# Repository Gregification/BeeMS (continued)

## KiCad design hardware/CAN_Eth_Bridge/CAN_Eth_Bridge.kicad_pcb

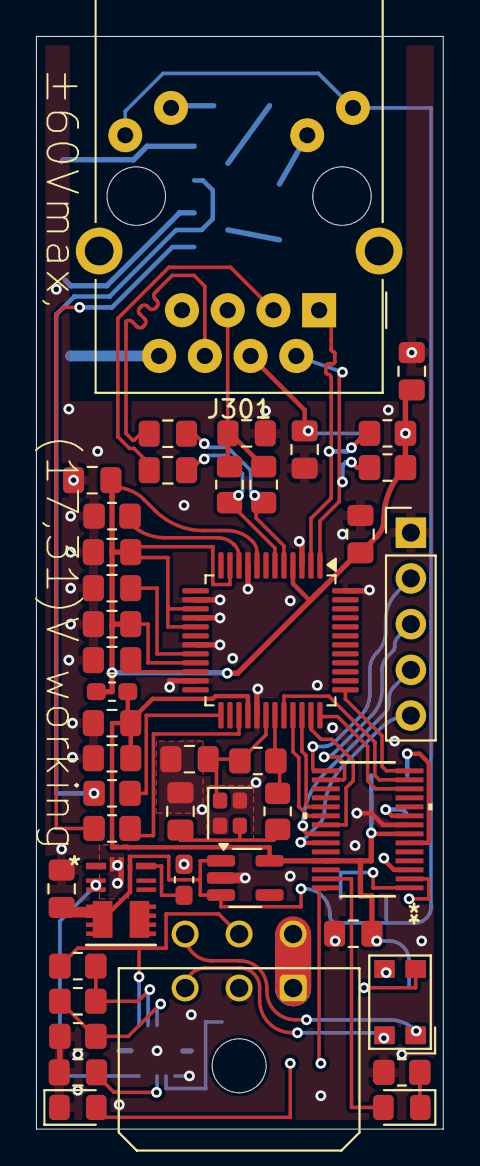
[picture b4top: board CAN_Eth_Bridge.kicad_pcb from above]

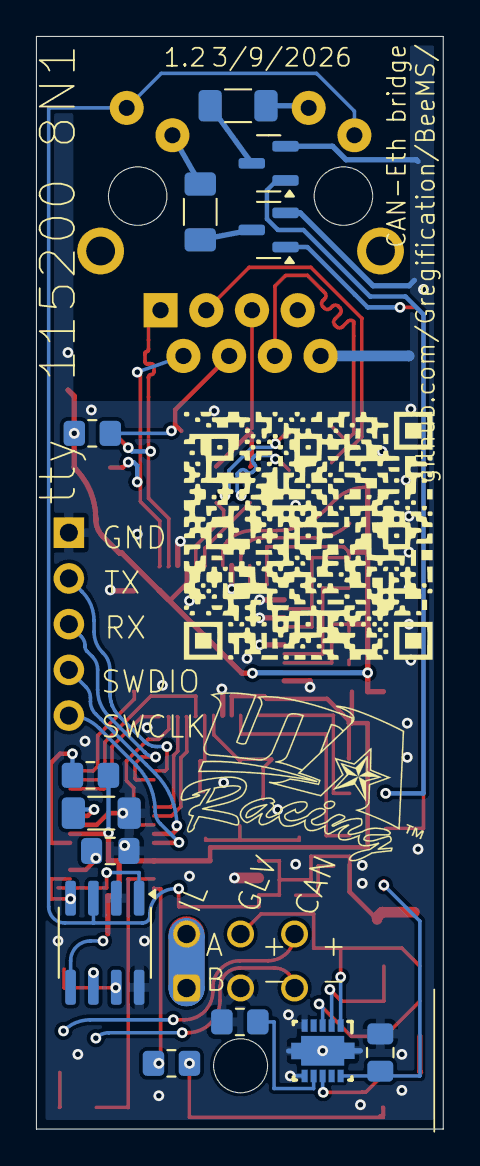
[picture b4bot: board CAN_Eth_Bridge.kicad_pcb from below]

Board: 2 copper layers, 22.6 x 60.7 mm, 57 parts (13 on the bottom side), 57 nets.

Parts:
C101: 1u; C_0603_1608Metric_Pad1.08x0.95mm_HandSolder
C102, C312, C319: 10n; C_0805_2012Metric_Pad1.18x1.45mm_HandSolder
C103, C105, C302, C309: 22u; C_0805_2012Metric_Pad1.18x1.45mm_HandSolder
C106, C110, C301, C304, C305, C311, C313: 220n; C_0805_2012Metric_Pad1.18x1.45mm_HandSolder
C303, C306: 18p; C_0805_2012Metric_Pad1.18x1.45mm_HandSolder
C314: 4.7u; C_0805_2012Metric_Pad1.18x1.45mm_HandSolder
C316, C317: 6.8n; C_0805_2012Metric_Pad1.18x1.45mm_HandSolder
C318: 22n; C_0805_2012Metric_Pad1.18x1.45mm_HandSolder
D102: green; LED_0805_2012Metric_Pad1.15x1.40mm_HandSolder
D105: blue; LED_0805_2012Metric_Pad1.15x1.40mm_HandSolder
FB301: MH1608-151Y; L_0603_1608Metric_Pad1.05x0.95mm_HandSolder
FL101: Choke_CommonMode_FerriteCore_1243; L_CommonModeChoke_Coilcraft_1812CAN
J101: Global LV and CAN; Molex_Micro-Fit_3.0_43045-0600_2x03_P3.00mm_Horizontal
J102: Conn_01x05_Pin; PinHeader_1x05_P2.54mm_Vertical
J301: RJ45_Amphenol_RJMG1BD3B8K1ANR
Q301, Q302: MMBT5550L; SOT-23
R101: 22.1k; R_0805_2012Metric_Pad1.20x1.40mm_HandSolder
R102, R103, R104, R311, R312: 2.4k; R_0805_2012Metric_Pad1.20x1.40mm_HandSolder
R105: 100k; R_1206_3216Metric_Pad1.30x1.75mm_HandSolder
R106: 40.2k; R_0805_2012Metric_Pad1.20x1.40mm_HandSolder
R107, R301: 1M; R_0805_2012Metric_Pad1.20x1.40mm_HandSolder
R108: 33.2k; R_0805_2012Metric_Pad1.20x1.40mm_HandSolder
R302, R315: 10; R_0805_2012Metric_Pad1.20x1.40mm_HandSolder
R303: 12.4k; R_0805_2012Metric_Pad1.20x1.40mm_HandSolder
R309, R310, R313, R314: 49.9; R_0805_2012Metric_Pad1.20x1.40mm_HandSolder
R316, R317: 750; R_1206_3216Metric_Pad1.30x1.75mm_HandSolder
U101: TPSM33606S5QRDNRQ1; RDN0011A_TEX
U102: TPS26625DRCR; DRC0010J_NV
U103: MCP2542FDxMF; SOIC-8_3.9x4.9mm_P1.27mm
U104: XMSM0G3507SDGS28R; VSSOP28_DGS_TEX-M
U106: NCP163ASN330T1G; SOT-23-5_HandSoldering
U301: W5500; LQFP-48_7x7mm_P0.5mm
Y301: Crystal_GND24; Crystal_SMD_2016-4Pin_2.0x1.6mm

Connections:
+3.3V: C105.1, C309.1, C313.1, FB301.1, R104.2, U103.5 (VIO), U104.7 (VDD), U104.25 (PA22/CLK_OUT/A0_7), U106.5 (VOUT), U301.28 (VDD)
+5V: C103.1, J301.L1, J301.L4, U101.4 (VOUT), U101.9 (FB), U103.3 (VDD), U106.1 (VIN), U106.3 (EN)
/Ethernet/+3.3VA: C301.1, C302.1, C304.1, C305.1, C311.1, FB301.2, R309.2, R313.2, R315.1, U301.4 (AVDD), U301.8 (AVDD), U301.11 (AVDD), U301.15 (AVDD), U301.17 (AVDD), U301.21 (AVDD)
/Ethernet/RD+: C316.2, J301.R3 (RD+)
/Ethernet/RD-: C317.2, J301.R6 (RD-)
/Ethernet/RX+: C316.1, R314.2, U301.6 (RXP)
/Ethernet/RX-: C317.1, R310.2, U301.5 (RXN)
/Ethernet/TD+: J301.R1 (TD+), R309.1, U301.2 (TXP)
/Ethernet/TD-: J301.R2 (TD-), R313.1, U301.1 (TXN)
/GLV+: J101.5, R107.2, U102.1 (IN)
/G_CAN+: FL101.1, J101.6
/G_CAN-: FL101.4, J101.3
/G_IL+: J101.1, J101.4
/LV+: C110.1, U101.2 (EN), U101.3 (VIN), U102.10 (OUT)
/can.rx: U103.4 (RXD), U104.2 (PA27/RTC_OUT/A0_0)
/can.tx: U103.1 (TXD), U104.1 (PA26/A0_1)
/eth.MISO/POCI: U104.19 (PA16/A1_1/FCC_IN), U301.34 (MISO)
/eth.MOSI/PICO: U104.21 (PA18/A1_3), U301.35 (MOSI)
/eth.SCLK: U104.20 (PA17/A1_2), U301.33 (SCLK)
/eth.cs_N: U104.13 (PA6/HFCLK_IN/HFXOUT), U301.32 (~SCS)
/eth.irq_N: U104.12 (PA5/HFXIN/FCC_IN), U301.36 (~INT)
/eth.reset_N: U104.14 (PA9_/_RTC_OUT_/_CLK_OUT), U301.37 (~RST)
/led.i1: R102.2, U104.28 (PA25/A0_2)
/led.sched: D105.2 (A), U104.27 (PA24/A0_3)
/prog.SWCLK: J102.5, U104.23 (PA20/SWCLK)
/prog.SWDIO: J102.4, U104.22 (PA19/SWDIO)
/prog.uart_ui_rx: J102.3, U104.16 (PA11)
/prog.uart_ui_tx: J102.2, U104.15 (PA10/CLK_OUT)
/vcore: C106.1, U104.3 (VCORE)
GND: C101.2, C102.2, C103.2, C105.2, C106.2, C110.2, C301.2, C302.2, C303.2, C304.2, C305.2, C306.2, C309.2, C311.2, C312.2, C313.2, C314.1, C318.2, C319.2, D102.1 (K), J101.2, J102.1, J301.R8, Q301.2 (E), Q302.2 (E), R101.1, R103.2, R105.1, R106.1, R303.2, U101.10 (GND), U101.11 (MODE/SYNCH), U102.5 (RTN), U102.6 (GND), U102.11 (PAD), U103.2 (VSS), U103.8 (STBY), U104.8 (VSS), U106.2 (GND), U301.3 (AGND), U301.9 (AGND), U301.14 (AGND), U301.16 (AGND), U301.19 (AGND), U301.23 (RSVD), U301.29 (GND), U301.48 (AGND), Y301.2, Y301.4
unnamed: C306.1, R302.1, Y301.3
unnamed: D102.2 (A), R102.1
unnamed: D105.1 (K), R103.1
unnamed: J301.L2, R316.2
unnamed: J301.L3, R317.2
unnamed: C319.1, J301.R5 (RCT), R310.1, R314.1
unnamed: C318.1, J301.R4 (TCT), R315.2
unnamed: Q301.1 (B), R311.1
unnamed: Q301.3 (C), R316.1
unnamed: Q302.1 (B), R312.1
unnamed: Q302.3 (C), R317.1
unnamed: C101.1, U101.8 (VCC)
unnamed: C102.1, U102.8 (DVDT)
unnamed: R101.2, U102.7 (ILIM)
unnamed: R106.2, R108.1, U102.3 (OVP)
unnamed: R107.1, R108.2, U102.2 (UVLO)
unnamed: FL101.2, U103.7 (CANH)
unnamed: FL101.3, U103.6 (CANL)
unnamed: R104.1, U104.6 (NRST)
unnamed: R105.2, U104.9 (PA2_/_ROSC)
unnamed: C312.1, U301.22 (1V2O)
unnamed: R312.2, U301.27 (ACTLED)
unnamed: R303.1, U301.10 (EXRES1)
unnamed: R311.2, U301.25 (LINKLED)
unnamed: C314.2, U301.20 (TOCAP)
unnamed: C303.1, R301.1, U301.30 (XI/CLKIN), Y301.1
unnamed: R301.2, R302.2, U301.31 (XO)

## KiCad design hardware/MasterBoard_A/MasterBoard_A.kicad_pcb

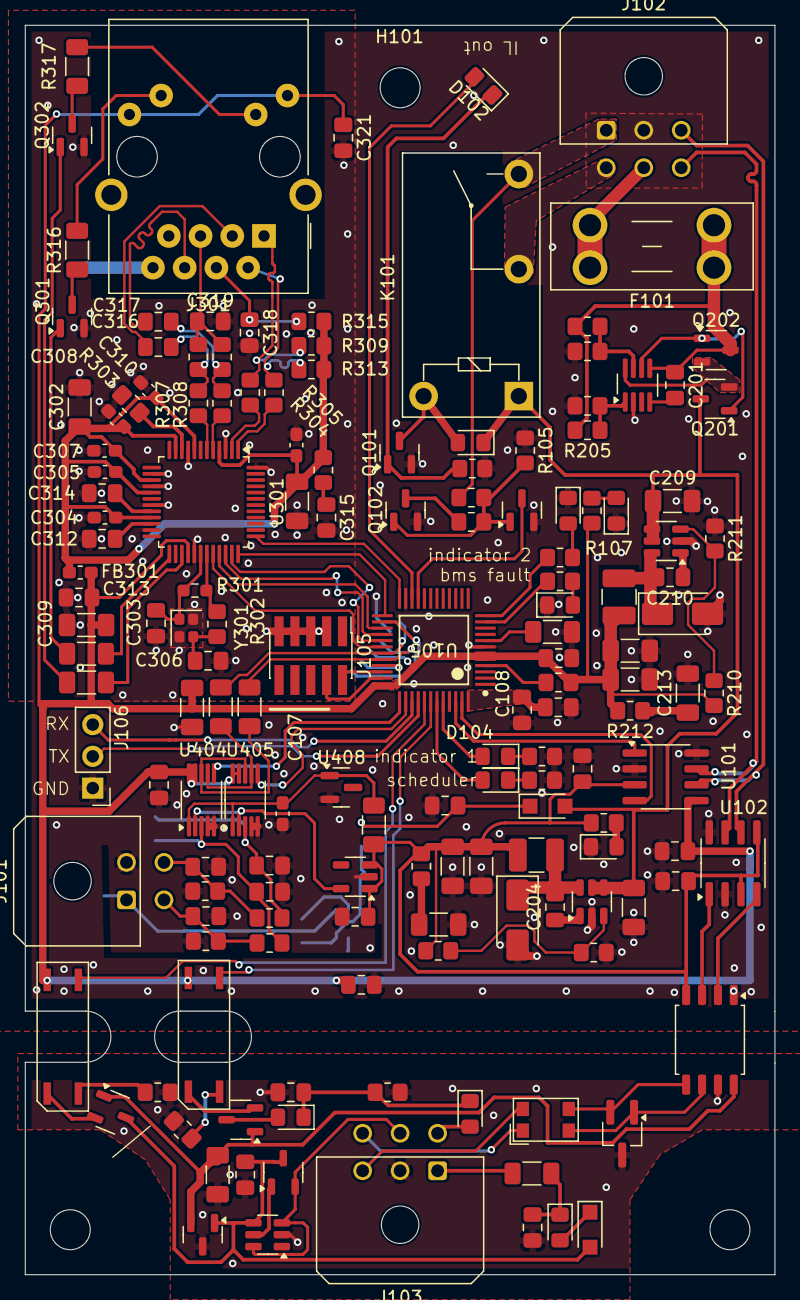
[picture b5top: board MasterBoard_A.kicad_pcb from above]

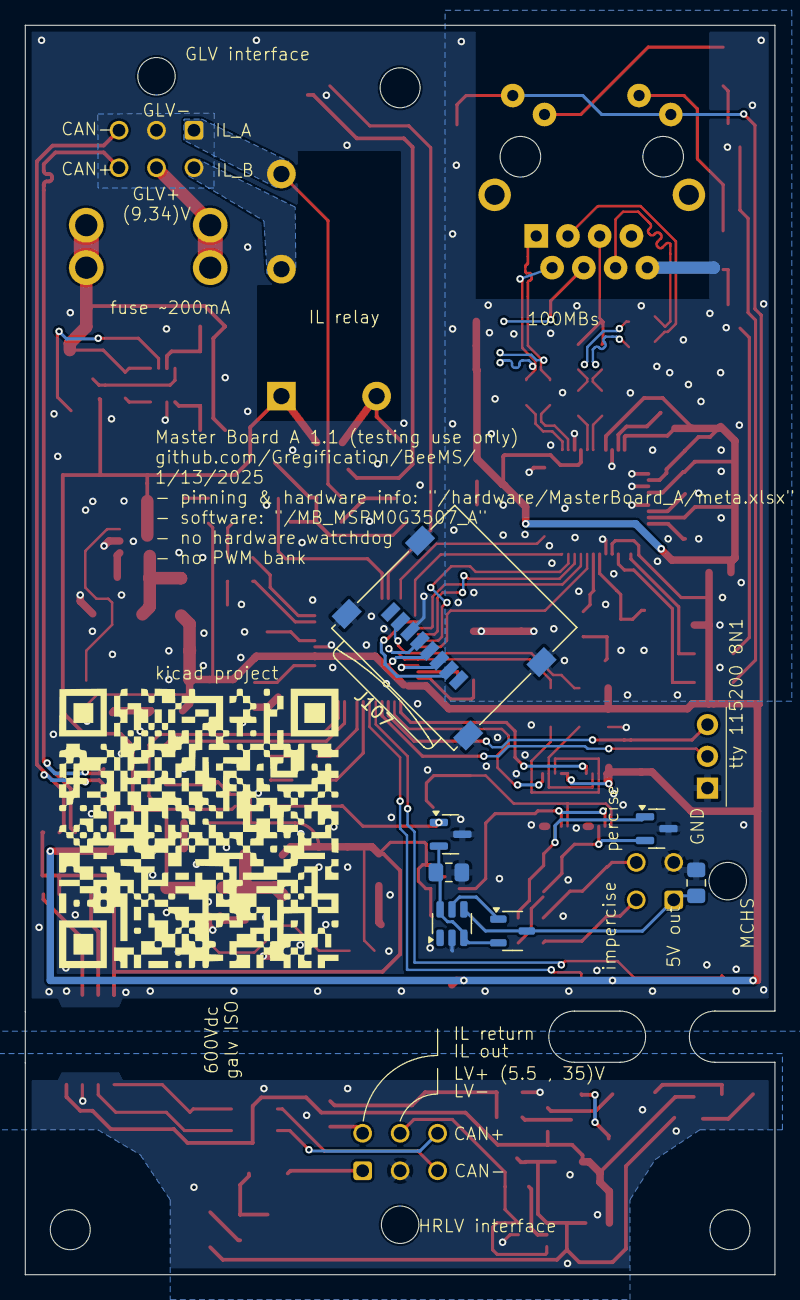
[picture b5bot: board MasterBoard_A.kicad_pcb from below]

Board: 2 copper layers, 60.0 x 100.0 mm, 166 parts (7 on the bottom side), 123 nets.

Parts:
C101, C102, C104, C108, C109, C110, C201, C204, C208, C210, C313, C315, C321, C402, C403, C407, C410, C411, C501, C502, C504: 220n; C_0805_2012Metric_Pad1.18x1.45mm_HandSolder
C107, C203, C205, C206, C207, C209, C211, C212, C213, C301, C302, C309, C503: 10u; C_1206_3216Metric_Pad1.33x1.80mm_HandSolder
C303, C306: 18p; C_0805_2012Metric_Pad1.18x1.45mm_HandSolder
C304, C305, C307, C308, C310, C311, C404: 100n; C_0603_1608Metric_Pad1.08x0.95mm_HandSolder
C312, C319, C405, C406, C408, C409: 10n; C_0805_2012Metric_Pad1.18x1.45mm_HandSolder
C314: 4.7u; C_0805_2012Metric_Pad1.18x1.45mm_HandSolder
C316, C317: 6.8n; C_0805_2012Metric_Pad1.18x1.45mm_HandSolder
C318: 22n; C_0805_2012Metric_Pad1.18x1.45mm_HandSolder
CR501: ESD2CAN36DBZRQ1; TSOT-23_HandSoldering
D101, D501, D503: TS4148; D_0805_2012Metric_Pad1.15x1.40mm_HandSolder
D102, D201, D202: green; LED_0805_2012Metric_Pad1.15x1.40mm_HandSolder
D103, D104: yellow; LED_0805_2012Metric_Pad1.15x1.40mm_HandSolder
D105: red; LED_0805_2012Metric_Pad1.15x1.40mm_HandSolder
D106: blue; LED_0805_2012Metric_Pad1.15x1.40mm_HandSolder
D203, D204: ES1D; D_SMA
D402: 3.9V; SOT-23
D504: 10V; D_0805_2012Metric_Pad1.15x1.40mm_HandSolder
F101: ~1A; Fuseholder_Blade_Mini_Keystone_3568
FB301: MH1608-151Y; L_0603_1608Metric_Pad1.05x0.95mm_HandSolder
FL101: Choke_CommonMode_FerriteCore_1243; L_CommonModeChoke_Coilcraft_1812CAN
H101, H102, H103: MountingHole; MountingHole_3.2mm_M3
J101: Main Current Hall Sensor; Molex_Micro-Fit_3.0_43045-0400_2x02_P3.00mm_Horizontal
J102: Global LV and CAN; Molex_Micro-Fit_3.0_43045-0600_2x03_P3.00mm_Horizontal
J103: HRLV; Molex_Micro-Fit_3.0_43045-0600_2x03_P3.00mm_Horizontal
J105: Conn_02x05_Odd_Even; PinHeader_2x05_P1.27mm_Vertical_SMD
J106: uart; PinHeader_1x03_P2.54mm_Vertical
J107: Micro_SD_Card; microSD_HC_Wuerth_693072010801
J301: RJ45_Amphenol_RJMG1BD3B8K1ANR
K101: G5Q-1A 24Vdc; Relay_SPST_Omron-G5Q-1A
L201, L202: 10u; L_1210_3225Metric_Pad1.42x2.65mm_HandSolder
Q101, Q102, Q103, Q301, Q302: MMBT5550L; SOT-23
Q201, Q202, Q402, Q501, Q502, Q503: TSM2328CX; SOT-23-3
R101, R105, R110, R203, R204, R402, R404: 3.32k; R_0805_2012Metric_Pad1.20x1.40mm_HandSolder
R102, R206, R208, R211: 22.1k; R_0805_2012Metric_Pad1.20x1.40mm_HandSolder
R103, R112, R311, R312, R316, R317, R504: 332; R_1206_3216Metric_Pad1.30x1.75mm_HandSolder
R104, R202, R207, R501: 88.7k; R_0805_2012Metric_Pad1.20x1.40mm_HandSolder
R106, R309, R310, R313, R314: 49.9; R_0805_2012Metric_Pad1.20x1.40mm_HandSolder
R107, R108, R109, R503, R506: 2.4k; R_0805_2012Metric_Pad1.20x1.40mm_HandSolder
R111: 100k; R_1206_3216Metric_Pad1.30x1.75mm_HandSolder
R201, R303, R406, R407: 12.4k; R_0805_2012Metric_Pad1.20x1.40mm_HandSolder
R205: 140k; R_0805_2012Metric_Pad1.20x1.40mm_HandSolder
R209, R212, R306, R315: 10; R_0805_2012Metric_Pad1.20x1.40mm_HandSolder
R210: 51k; R_0805_2012Metric_Pad1.20x1.40mm_HandSolder
R301: 1M; R_0603_1608Metric_Pad0.98x0.95mm_HandSolder
R302, R304, R305, R307, R308: 14.3; R_0805_2012Metric_Pad1.20x1.40mm_HandSolder
R405: 750; R_1206_3216Metric_Pad1.30x1.75mm_HandSolder
U101, U102: MCP2542FDxMF; SOIC-8_3.9x4.9mm_P1.27mm
U105: XM0G3507QPTRQ1; PT0048A-IPC_B
U202: LM74502; SOT-23-8_Handsoldering
U204, U205: AP64060ZQ; TSOT-23-6
U301: W5500; LQFP-48_7x7mm_P0.5mm
U401: AP7384-50SA; SOT-23
U402: TLV713185PDBV; SOT-23-5
U403, U501: NSI5030; Nexperia_CFP3_SOD-123W
U404, U405: MCP33151; MSOP-10_3x3mm_P0.5mm
U408: LM4040DBZ-4.1; SOT-23
U409, U503: NCV68061; TSOT-23-6
U502, U506: ISOM8110DFS; ISOM811_SOIC-4_DFG
U505: AP7375-50SA; SOT-23
U509: ISO1044BD; SOIC-8_5.3x5.3mm_P1.27mm
Y301: Crystal_GND24; Crystal_SMD_2016-4Pin_2.0x1.6mm

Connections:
+3.3V: C102.1, C107.1, C109.1, C208.1, C211.1, C212.1, C309.1, C313.1, C321.1, C403.1, FB301.1, J107.4 (VDD), J301.L1, J301.L4, L202.1, R102.2, R204.2, R210.2, R212.2, U101.5 (VIO), U105.5 (PA31_CLK_OUT), U105.6 (VDD), U105.36 (PB17_A1_4), U301.28 (VDD), U404.9 (SDI), U404.10 (DVio), U405.9 (SDI), U405.10 (DVio), U502.4 (C), U506.4 (C)
+5V: C101.1, C104.1, C205.1, C206.1, C402.1, L201.1, R201.1, R207.2, R209.2, R405.2, U101.3 (VDD), U102.3 (VDD), U102.5 (VIO), U402.1 (IN), U402.3 (EN), U509.4 (GND1)
/Ethernet/+3.3VA: C301.1, C302.1, C304.1, C305.1, C307.1, C308.1, C310.1, C311.1, FB301.2, R306.2, R309.2, R313.2, R315.1, U301.4 (AVDD), U301.8 (AVDD), U301.11 (AVDD), U301.15 (AVDD), U301.17 (AVDD), U301.21 (AVDD)
/Ethernet/RD+: C316.2, J301.R3 (RD+)
/Ethernet/RD-: C317.2, J301.R6 (RD-)
/Ethernet/RX+: R307.2, U301.6 (RXP)
/Ethernet/RX-: R308.1, U301.5 (RXN)
/Ethernet/RX_1+: C316.1, R307.1, R314.2
/Ethernet/RX_1-: C317.1, R308.2, R310.2
/Ethernet/TD+: J301.R1 (TD+), R304.1, R309.1
/Ethernet/TD-: J301.R2 (TD-), R305.2, R313.1
/Ethernet/TX+: R304.2, U301.2 (TXP)
/Ethernet/TX-: R305.1, U301.1 (TXN)
/GLV PSU/GLV+: C201.1, F101.1, Q202.3 (D), R202.2, R205.2, U202.5 (VS)
/GLV PSU/passing: Q201.2 (S), Q202.2 (S), U202.8 (SRC)
/GLV+: F101.2, J102.5
/G_CAN+: J102.6, U101.7 (CANH), U102.7 (CANH)
/G_CAN-: J102.3, U101.6 (CANL), U102.6 (CANL)
/G_IL+: J102.1, K101.3, R104.2
/G_IL-: J102.4, K101.2
/HRLV interface/+5V: C503.1, Q501.1 (G), Q502.1 (G), U505.2 (VO), U509.8 (VCC2)
/HRLV interface/CAN_RX: U102.1 (TXD), U509.3 (RXD)
/HRLV interface/CAN_TX: U102.4 (RXD), U509.2 (TXD)
/HRLV interface/LV+: C504.1, Q501.3 (D), Q503.3 (D), U501.2, U503.4 (D), U505.1 (VI)
/HRLV_CAN+: FL101.1, J103.6
/HRLV_CAN-: FL101.4, J103.3
/HRLV_IL+: J103.1, R504.2
/HRLV_IL-: D501.2 (A), J103.4
/HRLV_LV+: J103.5, Q503.2 (S), U503.3 (EN), U503.6 (S)
/HRLV_LV-: C501.2, C502.2, C503.2, C504.2, CR501.3 (GND), J103.2, R501.1, R503.1, R506.1, U503.2 (GND), U505.3 (GND), U509.7 (GND2)
/IL.forward: D102.2 (A), U105.22 (PB8)
/IL.sense: Q103.3 (C), U105.21 (PB7)
/MCHall_5Vin: C411.1, J101.1, Q402.3 (D), U409.4 (D)
/MCHall_imprecise: C408.1, J101.3, R402.2, R406.1
/MCHall_percise: C409.1, J101.4, R404.2, R407.1
/Main Current Hall Sensing/1.8VA: U402.5 (OUT), U404.2 (AVdd), U405.2 (AVdd)
/Main Current Hall Sensing/4.096Vref: C404.1, R405.1, U404.1 (Vref), U405.1 (Vref), U408.1 (K)
/Main Current Hall Sensing/SCLK: R112.2, U404.8 (SCLK), U405.8 (SCLK)
/Main Current Hall Sensing/SDO: R103.2, U404.7 (SDO), U405.7 (SDO)
/can.rx: U101.4 (RXD), U105.47 (PA27_RTC_OUT_A0_0)
/can.tx: U101.1 (TXD), U105.46 (PA26_A0_1)
/eth.MISO/POCI: U105.28 (PA13), U301.34 (MISO)
/eth.MOSI/PICO: U105.29 (PA14_CLK_OUT_A0_12), U301.35 (MOSI)
/eth.SCLK: U105.27 (PA12_FCC_IN), U301.33 (SCLK)
/eth.cs_N: U105.30 (PA15_A1_0), U301.32 (~SCS)
/eth.irq_N: U105.25 (PB15), U301.36 (~INT)
/eth.reset_N: U105.24 (PB14), U301.37 (~RST)
/hrlv.pres_hrlv: U105.41 (PB20_A0_6), U506.3 (E)
/hrlv.pres_interlock: U105.42 (PB24_A0_5), U502.3 (E)
/led.BMSFault: R109.2, U105.11 (PA5_HFXIN_FCC_IN)
/led.i1: D104.2 (A), U105.44 (PA24_A0_3)
/led.i2: R107.2, U105.12 (PA6_HFCLK_IN_HFXOUT)
/led.sched: D106.2 (A), U105.43 (PA23_VREF+)
/mchs.MISO/POCI: J107.7 (DAT0), R103.1, U105.31 (PA16_A1_1_FCC_IN)
/mchs.MOSI/PICO: J107.3 (CMD), U105.33 (PA18_A1_3)
/mchs.SCLK: J107.5 (CLK), R112.1, U105.32 (PA17_A1_2)
/mchs.cs_imp: U105.38 (PB19_A1_6), U405.6 (CNVST)
/mchs.cs_per: U105.37 (PB18_A1_5), U404.6 (CNVST)
/mchs.cs_sd: J107.2 (DAT3/CD), U105.26 (PB16)
/prog.SWCLK: J105.4, U105.35 (PA20_SWCLK)
/prog.SWDIO: J105.2, U105.34 (PA19_SWDIO)
/prog.uart_ui_rx: J106.2, U105.40 (PA22_CLK_OUT_A0_7)
/prog.uart_ui_tx: J106.3, U105.39 (PA21_A1_7_VREF-)
/vcore: C108.1, C110.1, U105.48 (VCORE)
GND: C101.2, C102.2, C104.2, C107.2, C108.2, C109.2, C110.2, C203.2, C205.2, C206.2, C207.2, C208.2, C209.2, C211.2, C212.2, C213.2, C301.2, C302.2, C303.2, C304.2, C305.2, C306.2, C307.2, C308.2, C309.2, C310.2, C311.2, C312.2, C313.2, C314.1, C315.2, C318.2, C319.2, C321.2, C402.2, C403.2, C404.2, C405.2, C406.2, C407.2, C408.2, C409.2, C410.2, C411.2, D103.1 (K), D105.1 (K), D201.1 (K), D202.1 (K), D203.2 (A), D204.2 (A), D402.3 (A), J101.2, J102.2, J105.3, J105.5, J105.7, J105.9, J106.1, J107.6 (VSS), J107.9 (SHIELD), J301.R8, Q101.2 (E), Q102.2 (E), Q103.2 (E), Q301.2 (E), Q302.2 (E), R101.1, R105.1, R108.2, R110.1, R111.1, R203.1, R206.1, R208.1, R211.1, R303.2, R406.2, R407.2, U101.2 (VSS), U101.8 (STBY), U102.2 (VSS), U102.8 (STBY), U105.7 (VSS), U105.23 (PB9), U202.2 (GND), U204.2 (GND), U205.2 (GND), U301.3 (AGND), U301.9 (AGND), U301.14 (AGND), U301.16 (AGND), U301.19 (AGND), U301.23 (RSVD), U301.29 (GND), U301.48 (AGND), U401.3 (GND), U402.2 (GND), U404.4 (Ain-), U404.5 (GND), U405.4 (Ain-), U405.5 (GND), U408.2 (A), U409.2 (GND), U509.1 (VCC1), Y301.2, Y301.4
LV+: C203.1, C209.1, D101.1 (K), K101.1, Q201.3 (D), U204.4 (EN), U204.5 (Vin), U205.4 (EN), U205.5 (Vin), U403.2
unnamed: C207.1, R209.1
unnamed: C213.1, R212.1
unnamed: C306.1, R302.1, Y301.3
unnamed: C315.1, R306.1
unnamed: D101.2 (A), K101.5, Q101.3 (C)
unnamed: D102.1 (K), Q101.1 (B), R101.2
unnamed: D103.2 (A), R107.1
unnamed: D104.1 (K), R108.1
unnamed: D105.2 (A), R109.1
unnamed: D106.1 (K), R110.2
unnamed: D201.2 (A), R201.2
unnamed: D202.2 (A), R204.1
unnamed: C204.2, D203.1 (K), L201.2, U204.6 (SW)
unnamed: C210.2, D204.1 (K), L202.2, U205.6 (SW)
unnamed: C501.1, D501.1 (K), D504.1 (K), R501.2
unnamed: D503.2 (A), U501.1
unnamed: C502.1, D503.1 (K), R504.1
unnamed: D504.2 (A), Q502.3 (D)
unnamed: J301.L2, R316.2
unnamed: J301.L3, R317.1
unnamed: C319.1, J301.R5 (RCT), R310.1, R314.1
unnamed: C318.1, J301.R4 (TCT), R315.2
unnamed: Q102.1 (B), Q103.1 (B), R104.1, R105.2, R106.2
unnamed: Q102.3 (C), R106.1
unnamed: Q201.1 (G), Q202.1 (G), U202.6 (GATE)
unnamed: Q301.1 (B), R311.1
unnamed: Q301.3 (C), R316.1
unnamed: Q302.1 (B), R312.1
unnamed: Q302.3 (C), R317.2
unnamed: Q402.1 (G), U409.5 (G)
unnamed: C407.1, Q402.2 (S), U401.2 (VO), U409.3 (EN), U409.6 (S)
unnamed: Q501.2 (S), U506.1 (+TX)
unnamed: Q502.2 (S), U502.1 (+TX)
unnamed: Q503.1 (G), U503.5 (G)
unnamed: R111.2, U105.8 (PA2_ROSC)
unnamed: R102.1, U105.4 (RST_N)
unnamed: R205.1, R206.2, U202.1 (EN/UVLO)
unnamed: R202.1, R203.2, U202.7 (OV)
unnamed: C201.2, U202.4 (VCAP)
unnamed: C204.1, U204.1 (BST)
unnamed: R207.1, R208.2, U204.3 (FB)
unnamed: C210.1, U205.1 (BST)
unnamed: R210.1, R211.2, U205.3 (FB)
unnamed: C312.1, U301.22 (1V2O)
unnamed: R312.2, U301.27 (ACTLED)
unnamed: R303.1, U301.10 (EXRES1)
unnamed: R311.2, U301.25 (LINKLED)
unnamed: C314.2, U301.20 (TOCAP)
unnamed: C303.1, R301.1, U301.30 (XI/CLKIN), Y301.1
unnamed: R301.2, R302.2, U301.31 (XO)
unnamed: C410.1, U401.1 (VI), U403.1
unnamed: C405.1, D402.2 (K), R402.1, U404.3 (Ain+)
unnamed: C406.1, D402.1 (K), R404.1, U405.3 (Ain+)
unnamed: R506.2, U502.2 (-TX)
unnamed: R503.2, U506.2 (-TX)
unnamed: CR501.1 (IO), FL101.2, U509.6 (CANH)
unnamed: CR501.2 (IO), FL101.3, U509.5 (CANL)

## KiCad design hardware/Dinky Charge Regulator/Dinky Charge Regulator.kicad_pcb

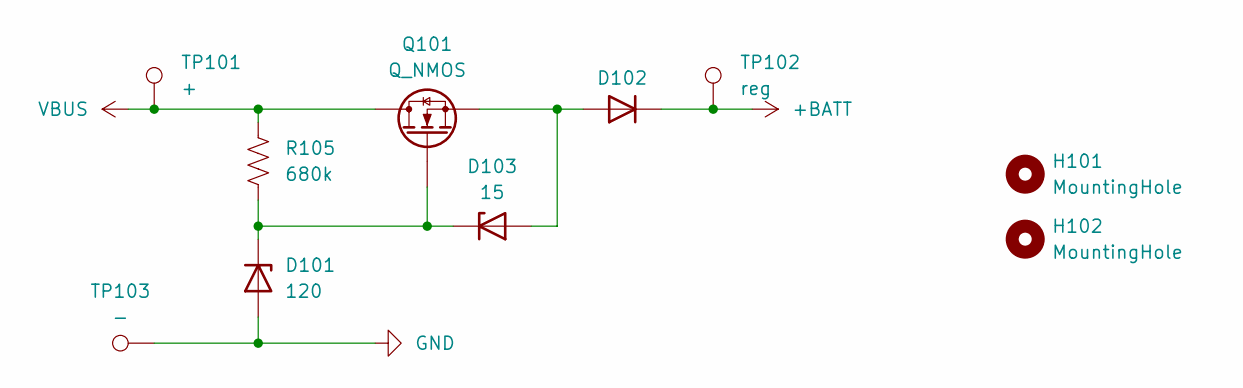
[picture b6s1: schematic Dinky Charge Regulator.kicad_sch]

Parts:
D101: 120; D_DO-41_SOD81_P12.70mm_Horizontal
D102: D_DO-41_SOD81_P12.70mm_Horizontal
D103: 15; D_DO-41_SOD81_P12.70mm_Horizontal
H101, H102: MountingHole; MountingHole_3.5mm
Q101: Q_NMOS; TO-247-3_Horizontal_TabDown
R105: 680k; R_Axial_DIN0411_L9.9mm_D3.6mm_P12.70mm_Horizontal
TP101: +; PinHeader_1x01_P2.54mm_Vertical
TP102: reg; PinHeader_1x01_P2.54mm_Vertical
TP103: -; PinHeader_1x01_P2.54mm_Vertical

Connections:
+BATT: D102.1 (K), TP102.1
GND: D101.2 (A), TP103.1
unnamed: D101.1 (K), D103.1 (K), Q101.1 (G), R105.1
unnamed: D102.2 (A), D103.2 (A), Q101.3 (S)
VBUS: Q101.2 (D), R105.2, TP101.1

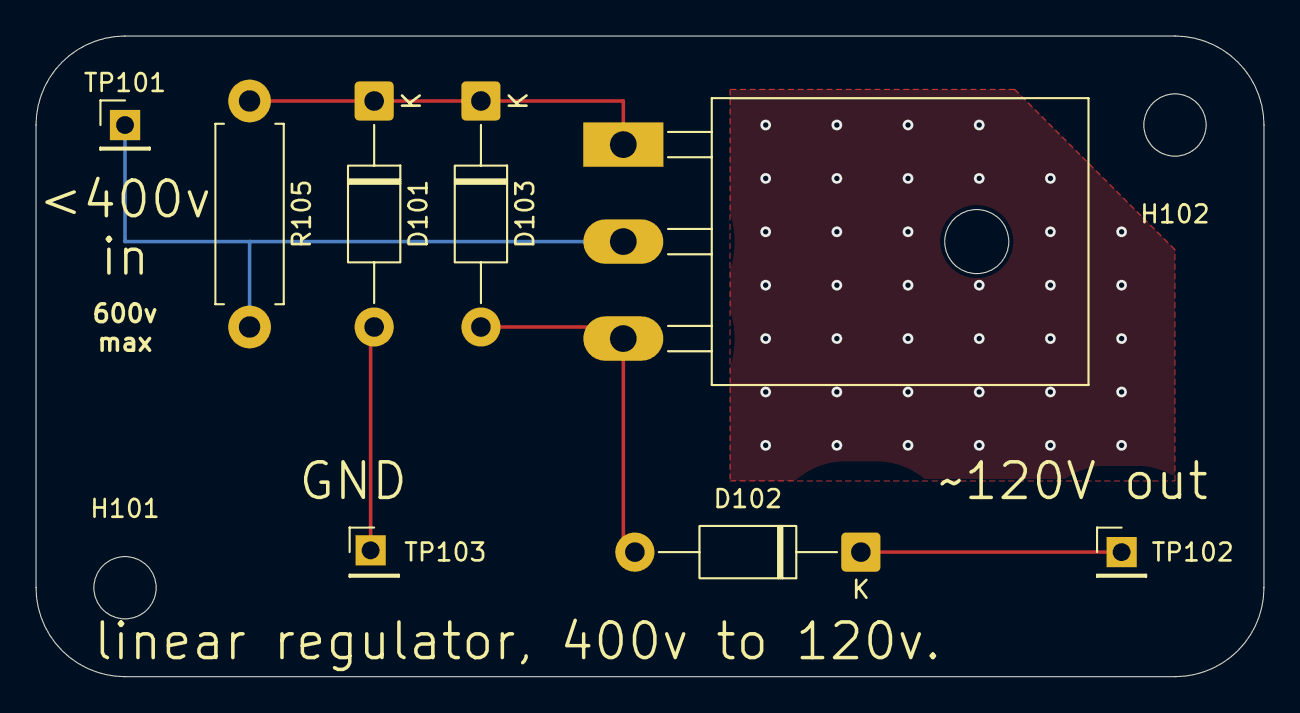
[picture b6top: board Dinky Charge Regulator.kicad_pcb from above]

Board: 2 copper layers, 69.0 x 36.0 mm, 10 parts (0 on the bottom side), 5 nets.

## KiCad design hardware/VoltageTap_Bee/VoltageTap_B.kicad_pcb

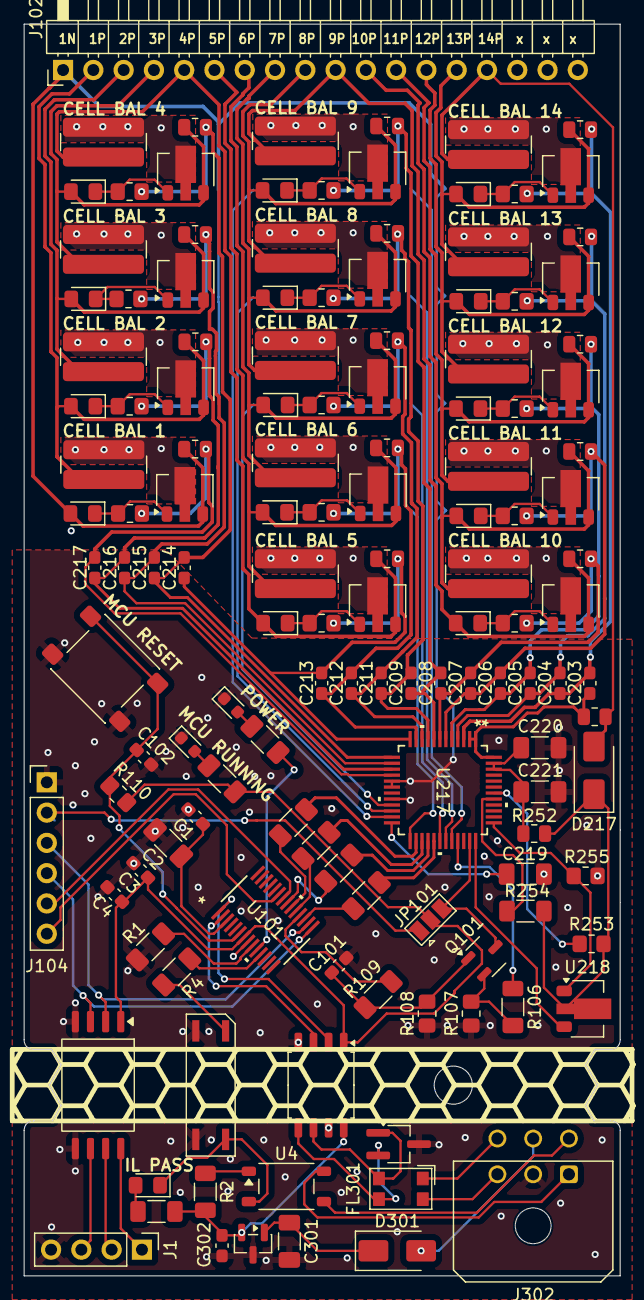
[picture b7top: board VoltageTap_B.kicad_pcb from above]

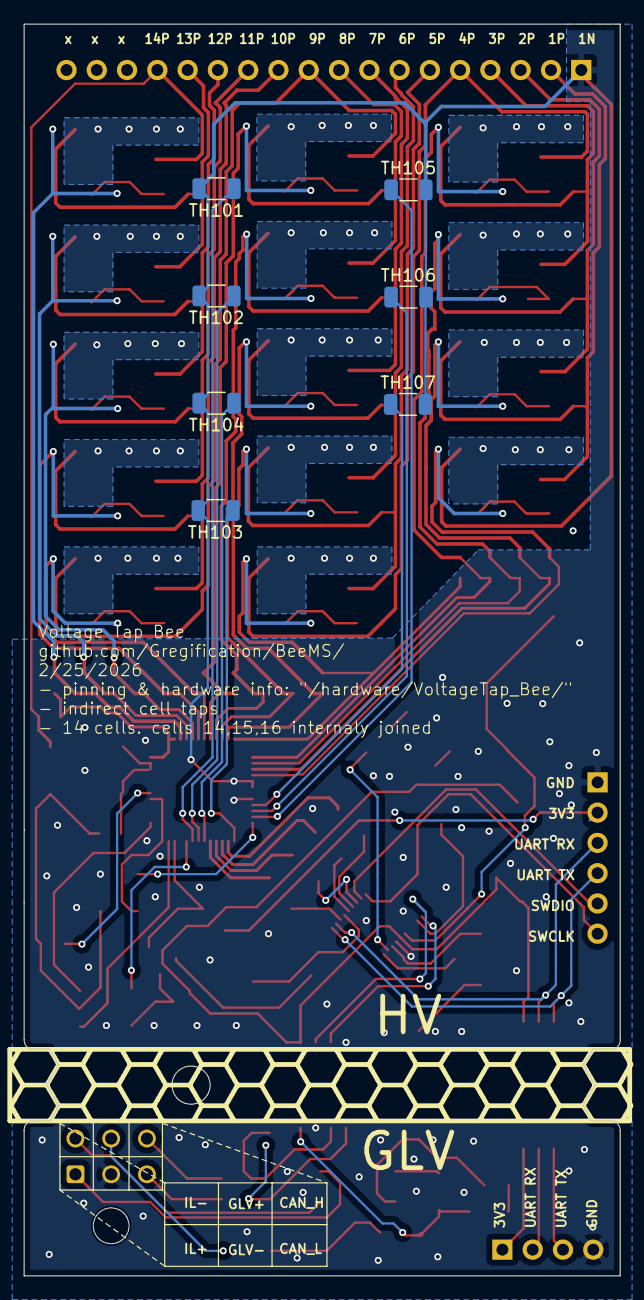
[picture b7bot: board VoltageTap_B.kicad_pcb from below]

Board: 2 copper layers, 50.0 x 105.0 mm, 145 parts (7 on the bottom side), 117 nets.

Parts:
C1, C3, C4, C101, C102, C203, C204, C205, C206, C207, C208, C209, C211, C212, C213, C214, C215, C216, C217, C302: 100n; C_0603_1608Metric_Pad1.08x0.95mm_HandSolder
C2, C219: 10u; C_1206_3216Metric_Pad1.33x1.80mm_HandSolder
C220, C221, C301: 1u; C_1206_3216Metric_Pad1.33x1.80mm_HandSolder
CR301: ESD2CAN36DBZRQ1; TSOT-23_HandSoldering
D1: green; LED_0805_2012Metric_Pad1.15x1.40mm_HandSolder
D101, D102: LED; LED_0603_1608Metric
D203, D204, D205, D206, D207, D208, D209, D210, D211, D212, D213, D214, D215, D216: TS4148; D_0805_2012Metric_Pad1.15x1.40mm_HandSolder
D217, D301: ES1D; D_SMA
FL301: Choke_CommonMode_FerriteCore_1243; L_CommonModeChoke_Coilcraft_1812CAN
H101: MountingHole; MountingHole_3.2mm_M3
J1: Conn_01x04_Pin; PinHeader_1x04_P2.54mm_Vertical
J102: Conn_01x18_Pin; PinHeader_1x18_P2.54mm_Horizontal
J104: Conn_01x06_Pin; PinHeader_1x06_P2.54mm_Vertical
J302: HRLV; Molex_Micro-Fit_3.0_43045-0600_2x03_P3.00mm_Horizontal
JP101: SolderJumper_3_Open; SolderJumper-3_P1.3mm_Open_Pad1.0x1.5mm
Q101: TSM2328CX; SOT-23-3
R1: 100k; R_1206_3216Metric_Pad1.30x1.75mm_HandSolder
R2, R3, R4, R101, R102, R103, R104, R105, R111: 750; R_1206_3216Metric_Pad1.30x1.75mm_HandSolder
R106, R109, R254: 4.99k; R_1206_3216Metric_Pad1.30x1.75mm_HandSolder
R107, R108, R110: 88.7k; R_0805_2012Metric_Pad1.20x1.40mm_HandSolder
R203, R204, R205, R206, R207, R208, R209, R228, R229, R230, R231, R232, R233, R234: 36; imperial wide resistor R_ 3264
R212, R213, R214, R215, R216, R217, R218, R237, R238, R239, R240, R241, R242, R243, R244, R252: 100; R_0805_2012Metric
R221, R222, R223, R224, R225, R226, R227, R245, R246, R247, R248, R249, R250, R251: 226; R_0805_2012Metric_Pad1.20x1.40mm_HandSolder
R253, R255: 10k; R_0805_2012Metric_Pad1.20x1.40mm_HandSolder
SW101: SW_Push; SW_SPST_PTS645Sx43SMTR92
TH101, TH102, TH103, TH104, TH105, TH106, TH107: Thermistor; R_1206_3216Metric
U2: STISO620; SOIC-8_7.5x5.85mm_P1.27mm
U3: ISOM8110DFS; ISOM811_SOIC-4_DFG
U4: TLP176AM; Toshiba_SOIC-4-6_4.4x3.6mm_P1.27mm
U101: XMSM0G3507SDGS28R; VSSOP28_DGS_TEX-M
U203, U204, U205, U206, U207, U208, U209, U210, U211, U212, U213, U214, U215, U216: 2PD2150-QX; SOT-89-3
U217: PBQ76952PFBT; BQ76952_PFB48_TEX
U218: FCX495; SOT-89-3
U302: ISO1044BD; SOIC-8_5.3x5.3mm_P1.27mm
U304: AP7384-50SA; SOT-23

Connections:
+BATT: D217.2 (A), J102.15, R203.2, R212.2
-BATT: C1.2, C2.2, C3.2, C4.2, C101.2, C102.2, C219.2, C220.2, C221.2, D101.1 (K), D102.1 (K), D216.2 (A), J102.1, J104.1, R1.2, R107.1, R108.1, R244.2, R255.1, SW101.2, TH101.2, TH102.2, TH103.2, TH104.2, TH105.2, TH106.2, TH107.2, U2.4 (GND1), U3.2 (-TX), U101.8 (VSS), U216.3 (E), U217.17 (VSS), U217.18 (SRP), U217.20 (SRN), U302.4 (GND1)
/BQ76952 1/1P: D215.2 (A), J102.2, R234.2, R243.2, U215.3 (E)
/BQ76952 1/2P: D214.2 (A), J102.3, R233.2, R242.2, U214.3 (E)
/BQ76952 1/3P: D213.2 (A), J102.4, R232.2, R241.2, U213.3 (E)
/BQ76952 1/4P: D212.2 (A), J102.5, R231.2, R240.2, U212.3 (E)
/BQ76952 1/5P: D211.2 (A), J102.6, R230.2, R239.2, U211.3 (E)
/BQ76952 1/6P: D210.2 (A), J102.7, R229.2, R238.2, U210.3 (E)
/BQ76952 1/7P: D209.2 (A), J102.8, R228.2, R237.2, U209.3 (E)
/BQ76952 1/8P: D208.2 (A), J102.9, R209.2, R218.2, U208.3 (E)
/BQ76952 1/9P: D207.2 (A), J102.10, R208.2, R217.2, U207.3 (E)
/BQ76952 1/10P: D206.2 (A), J102.11, R207.2, R216.2, U206.3 (E)
/BQ76952 1/11P: D205.2 (A), J102.12, R206.2, R215.2, U205.3 (E)
/BQ76952 1/12P: D204.2 (A), J102.13, R205.2, R214.2, U204.3 (E)
/BQ76952 1/13P: D203.2 (A), J102.14, R204.2, R213.2, U203.3 (E)
/BQ76952 1/ALERT: TH103.1, U217.25 (ALERT)
/BQ76952 1/BAT: C220.1, C221.1, R252.1, U217.46 (CP1), U217.47 (BAT)
/BQ76952 1/C1Jc: R234.1, U216.2 (C)
/BQ76952 1/C2Jc: R233.1, U215.2 (C)
/BQ76952 1/C3Jc: R232.1, U214.2 (C)
/BQ76952 1/C4Jc: R231.1, U213.2 (C)
/BQ76952 1/C5Jc: R230.1, U212.2 (C)
/BQ76952 1/C6Jc: R229.1, U211.2 (C)
/BQ76952 1/C7Jc: R228.1, U210.2 (C)
/BQ76952 1/C8Jc: R209.1, U209.2 (C)
/BQ76952 1/C9Jc: R208.1, U208.2 (C)
/BQ76952 1/C10Jc: R207.1, U207.2 (C)
/BQ76952 1/C11Jc: R206.1, U206.2 (C)
/BQ76952 1/C12Jc: R205.1, U205.2 (C)
/BQ76952 1/C13Jc: R204.1, U204.2 (C)
/BQ76952 1/C14Jc: R203.1, U203.2 (C)
/BQ76952 1/CFETOFF: R101.2, U217.29 (CFETOFF)
/BQ76952 1/DCHG: TH102.1, U217.31 (DCHG)
/BQ76952 1/DDSG: TH101.1, U217.32 (DDSG)
/BQ76952 1/DFETOFF: TH104.1, U217.30 (DFETOFF)
/BQ76952 1/HDQ: R103.2, U217.28 (HDQ)
/BQ76952 1/RST_SHUT: R106.1, U217.33 (RST_SHUT)
/BQ76952 1/SCL: R102.1, U217.26 (SCL)
/BQ76952 1/SDA: R104.1, U217.27 (SDA)
/BQ76952 1/TS1: TH107.1, U217.21 (TS1)
/BQ76952 1/TS2: TH106.1, U217.22 (TS2)
/BQ76952 1/TS3: TH105.1, U217.23 (TS3)
/GLV/3v3: J1.1, U2.8 (VDD2)
/GLV/5v: C302.1, R2.2, R3.2, U302.8 (VCC2), U304.2 (VO)
/GLV/CAN_H: FL301.1, J302.6
/GLV/CAN_L: FL301.4, J302.3
/GLV/GLV+: D301.2 (A), J302.5
/GLV/GLV-: C301.2, C302.2, CR301.3 (GND), J1.4, J302.2, U2.5 (GND2), U3.3 (E), U302.7 (GND2), U304.3 (GND)
/GLV/IL+: J302.1, U4.6
/GLV/IL-: J302.4, U4.4
/GLV/UART_RX: J1.2, U2.7 (TXB)
/GLV/UART_TX: J1.3, U2.6 (RXA)
/XDS_3v_supply: J104.2, JP101.1 (A)
BLINK: R111.2, U101.10 (PA3_/_LFXIN)
IL_EN: R4.1, U101.11 (PA4_/_LFCLK_IN_/_LFXOUT)
unnamed: D1.2 (A), R3.1
unnamed: D1.1 (K), U3.4 (C), U4.3
unnamed: D101.2 (A), R105.1
unnamed: D102.2 (A), R111.1
unnamed: D203.1 (K), R221.2, U203.1 (B)
unnamed: D204.1 (K), R222.2, U204.1 (B)
unnamed: D205.1 (K), R223.2, U205.1 (B)
unnamed: D206.1 (K), R224.2, U206.1 (B)
unnamed: D207.1 (K), R225.2, U207.1 (B)
unnamed: D208.1 (K), R226.2, U208.1 (B)
unnamed: D209.1 (K), R227.2, U209.1 (B)
unnamed: D210.1 (K), R245.2, U210.1 (B)
unnamed: D211.1 (K), R246.2, U211.1 (B)
unnamed: D212.1 (K), R247.2, U212.1 (B)
unnamed: D213.1 (K), R248.2, U213.1 (B)
unnamed: D214.1 (K), R249.2, U214.1 (B)
unnamed: D215.1 (K), R250.2, U215.1 (B)
unnamed: D216.1 (K), R251.2, U216.1 (B)
unnamed: D217.1 (K), R252.2, R253.2, R254.1, U218.2
unnamed: C301.1, D301.1 (K), U304.1 (VI)
unnamed: C101.1, Q101.1 (G), R108.2, R109.1
unnamed: Q101.2 (S), R106.2, R107.2
unnamed: R2.1, U4.1
unnamed: R4.2, U3.1 (+TX)
unnamed: R1.1, U101.9 (PA2_/_ROSC)
unnamed: C1.1, C2.1, U101.3 (VCORE)
unnamed: R255.2, U217.37 (BREG), U218.1
unnamed: R254.2, U217.41 (LD)
unnamed: R253.1, U217.42 (PACK)
unnamed: C219.1, U217.24 (REG18)
unnamed: U217.36 (REGIN), U218.3
unnamed: C217.2, R244.1, R251.1, U217.16 (VC0)
unnamed: C216.2, C217.1, R243.1, R250.1, U217.15 (VC1)
unnamed: C215.2, C216.1, R242.1, R249.1, U217.14 (VC2)
unnamed: C214.2, C215.1, R241.1, R248.1, U217.13 (VC3)
unnamed: C213.2, C214.1, R240.1, R247.1, U217.12 (VC4)
unnamed: C212.2, C213.1, R239.1, R246.1, U217.11 (VC5)
unnamed: C211.2, C212.1, R238.1, R245.1, U217.10 (VC6)
unnamed: C209.2, C211.1, R227.1, R237.1, U217.9 (VC7)
unnamed: C208.2, C209.1, R218.1, R226.1, U217.8 (VC8)
unnamed: C207.2, C208.1, R217.1, R225.1, U217.7 (VC9)
unnamed: C206.2, C207.1, R216.1, R224.1, U217.6 (VC10)
unnamed: C205.2, C206.1, R215.1, R223.1, U217.5 (VC11)
unnamed: C204.2, C205.1, R214.1, R222.1, U217.4 (VC12)
unnamed: C203.2, C204.1, R213.1, R221.1, U217.3 (VC13)
unnamed: C203.1, R212.1, U217.1 (VC15), U217.2 (VC14), U217.48 (VC16)
unnamed: CR301.1 (IO), FL301.2, U302.6 (CANH)
unnamed: CR301.2 (IO), FL301.3, U302.5 (CANL)
PA10_UART0-TX_XDS: J104.4, U2.3 (TXA), U101.15 (PA10/CLK_OUT)
PA11_UART0-RX_XDS: J104.3, U2.2 (RXB), U101.16 (PA11)
PA15_BBQ_RESET: R109.2, U101.18 (PA15/A1_0)
PA16_SPI1_MISO: R104.2, U101.19 (PA16/A1_1/FCC_IN)
PA17_SPI1_SCK: R102.2, U101.20 (PA17/A1_2)
PA18_SPI1_MOSI: R103.1, U101.21 (PA18/A1_3)
PA19_SWDIO: J104.5, U101.22 (PA19/SWDIO)
PA20_SWCLK: J104.6, U101.23 (PA20/SWCLK)
PA26_CAN_TX: U101.1 (PA26/A0_1), U302.2 (TXD)
PA27_CAN_RX: U101.2 (PA27/RTC_OUT/A0_0), U302.3 (RXD)
PB14_BBQ_CS: R101.1, U101.17 (PA14/CLK_OUT/A0_12)
RST_N: C102.1, R110.1, SW101.1, U101.6 (NRST)
VDD: C3.1, C4.1, JP101.2 (C), R105.2, R110.2, U2.1 (VDD1), U101.7 (VDD), U302.1 (VCC1)
onboard 3.3v src: JP101.3 (B), Q101.3 (D), U217.35 (REG1)
